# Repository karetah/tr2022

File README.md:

This is a tracktor, baby.

Reverse eng of some board.

Tools:

Kicad, drawio, 
CircuitJS1 http://www.falstad.com/circuit/

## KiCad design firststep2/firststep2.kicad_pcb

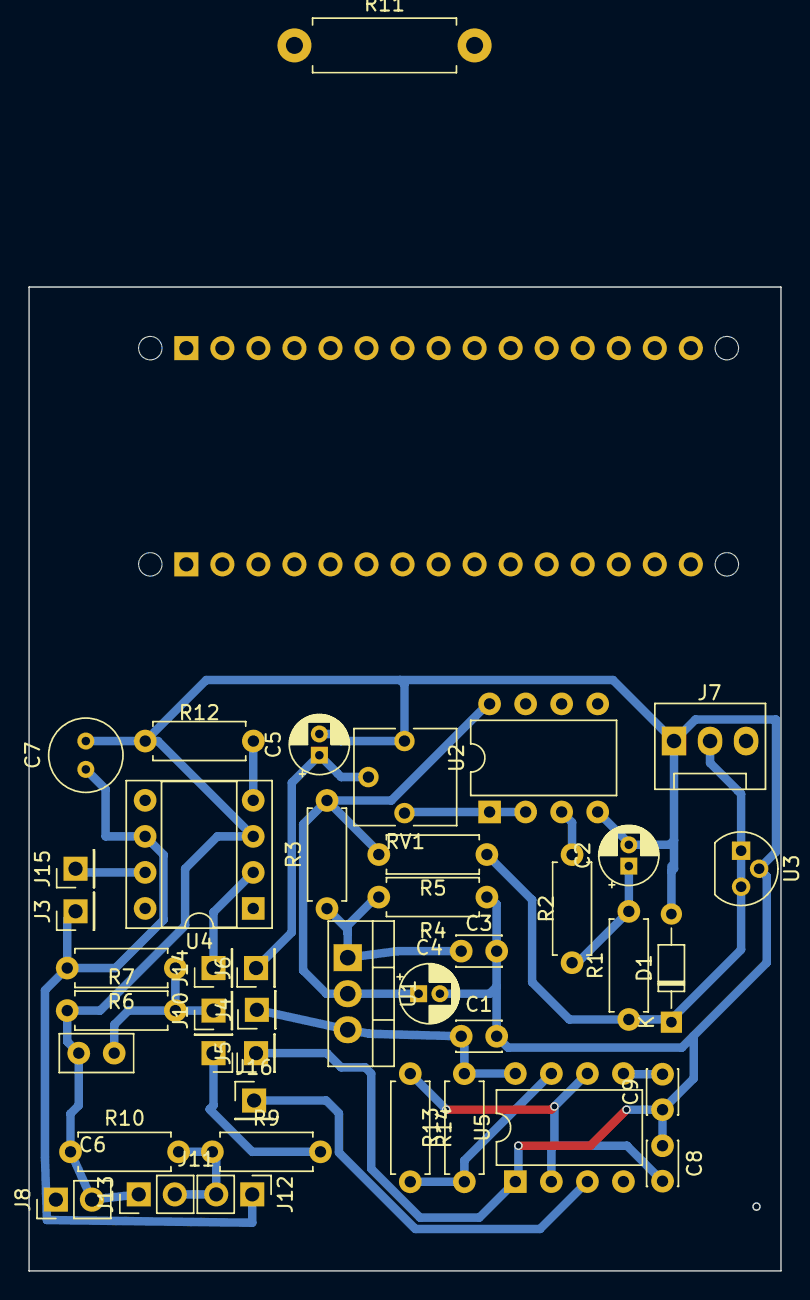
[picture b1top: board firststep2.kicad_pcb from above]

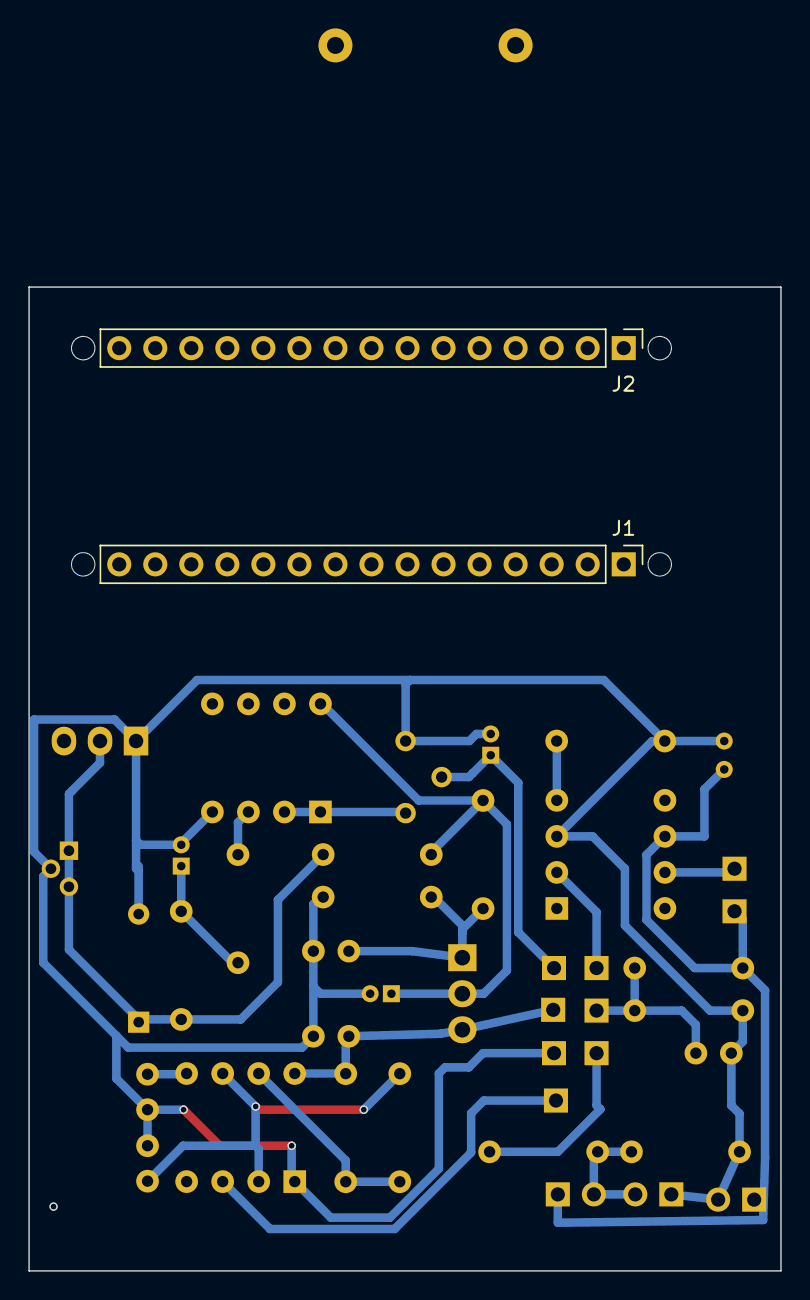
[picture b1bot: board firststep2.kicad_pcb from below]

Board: 2 copper layers, 53.0 x 69.3 mm, 48 parts (2 on the bottom side), 21 nets.

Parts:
C1, C9: 10n; C_Disc_D3.0mm_W2.0mm_P2.50mm
C2: 3,3u; CP_Radial_D4.0mm_P1.50mm
C3: 100n; C_Disc_D3.0mm_W2.0mm_P2.50mm
C4, C5: 1u; CP_Radial_D4.0mm_P1.50mm
C6: 100n; C_Disc_D5.0mm_W2.5mm_P2.50mm
C7: 10u; C_Radial_D5.0mm_H5.0mm_P2.00mm
C8: 6.8n; C_Disc_D3.0mm_W2.0mm_P2.50mm
D1: D_Zener; D_DO-34_SOD68_P7.62mm_Horizontal
J1: Analog; PinHeader_1x15_P2.54mm_Vertical
J2: Conn_01x03_Male; FanPinHeader_1x03_P2.54mm_Vertical
J2#2: Digital; PinHeader_1x15_P2.54mm_Vertical
J3: POWER12; PinHeader_1x01_P2.54mm_Vertical
J4: Conn_5V; PinHeader_1x01_P2.54mm_Vertical
J5: Conn_GND; PinHeader_1x01_P2.54mm_Vertical
J6: Arduino_A6; PinHeader_1x01_P2.54mm_Vertical
J8: BACKLAMP; PinHeader_1x02_P2.54mm_Vertical
J10: Arduino_A7; PinHeader_1x01_P2.54mm_Vertical
J11: Arduino_D6; PinHeader_1x01_P2.54mm_Vertical
J12: RELAY_SW; PinHeader_1x02_P2.54mm_Vertical
J13: RELAY_PWR; PinHeader_1x02_P2.54mm_Vertical
J14: Arduino_D9; PinHeader_1x01_P2.54mm_Vertical
J15: Conn_FET; PinHeader_1x01_P2.54mm_Vertical
J16: Arduino_RX0; PinHeader_1x01_P2.54mm_Vertical
MH1, MH2, MH3, MH4: MountingHole_65mil
R2, R2#2, R3: 330; R_Axial_DIN0207_L6.3mm_D2.5mm_P7.62mm_Horizontal
R4: 470; R_Axial_DIN0207_L6.3mm_D2.5mm_P7.62mm_Horizontal
R5, R13, R14: 1K; R_Axial_DIN0207_L6.3mm_D2.5mm_P7.62mm_Horizontal
R6: 150K; R_Axial_DIN0207_L6.3mm_D2.5mm_P7.62mm_Horizontal
R7, R12: 10K; R_Axial_DIN0207_L6.3mm_D2.5mm_P7.62mm_Horizontal
R9, R10: 22K; R_Axial_DIN0207_L6.3mm_D2.5mm_P7.62mm_Horizontal
R11: 10; R_Axial_DIN0411_L9.9mm_D3.6mm_P12.70mm_Horizontal
RV1: 20K; Potentiometer_Vishay_T73YP_Vertical
U1: LM317_TO-220; TO-220-3_Vertical
U2: TL431LP; TO-92
U2#2: TL072; DIP-8_W7.62mm
U4: MIC4428; DIP-8_W7.62mm_Socket
U5: NE555P; DIP-8_W7.62mm

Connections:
+5V: C1.1, J1.12, J4.1, R13.2, U1.3 (VI), U5.8 (VCC)
/D1/TX: J2#2.15, J16.1, U5.3 (Q)
/accel/A6: C5.1, J6.1, RV1.2
/accel/A7: C6.1, J10.1, R6.1, R7.2
/accel/amp: D1.1 (K), J2.2, R2.1, R5.1, U2.1 (REF), U2.3 (K)
/driver/*D6: J11.1, R9.2
/driver/*D9: J14.1, U4.2 (IN_A)
/~RESET: J1.13, J2#2.13
GND: C1.2, C2.2, C3.2, C4.2, C5.2, C6.2, C7.2, C8.1, C9.1, D1.2 (A), J1.14, J2.1, J2#2.12, J5.1, J8.2, J13.1, R4.1, R7.1, R10.1, R12.1, RV1.1, U2.2 (A), U2#2.4 (V-), U4.3 (GND), U5.1 (GND)
unnamed: C2.1, R2.2, R2#2.1
unnamed: C3.1, R3.1, R4.2, U1.1 (ADJ)
unnamed: C4.1, R3.2, R5.2, U1.2 (VO), U2#2.8 (V+)
unnamed: J12.2, J13.2, R9.1, R10.2
unnamed: J15.1, U4.7 (~OUT_A)
unnamed: R2#2.2, U2#2.3 (+)
unnamed: R12.2, U4.4 (IN_B)
unnamed: RV1.3, U2#2.1, U2#2.2 (-)
unnamed: C8.2, R14.1, U5.2 (TR), U5.6 (THR)
unnamed: C9.2, U5.5 (CV)
unnamed: R13.1, R14.2, U5.7 (DIS)
VCC: C7.1, J1.15, J3.1, J8.1, J12.1, R6.2, U4.6 (V+)

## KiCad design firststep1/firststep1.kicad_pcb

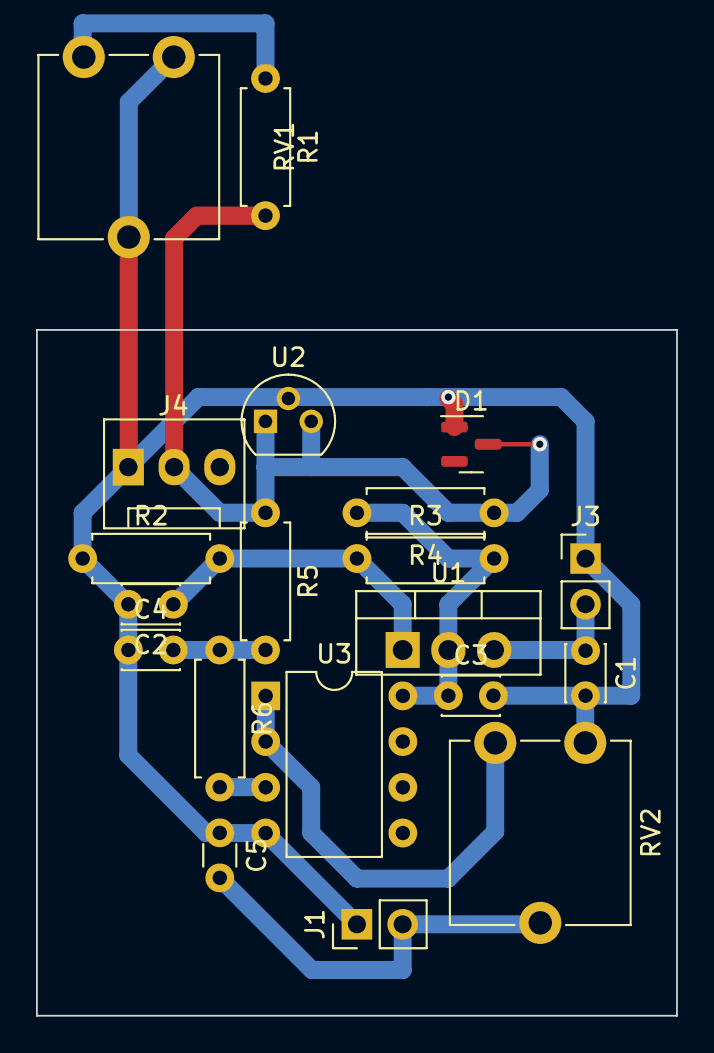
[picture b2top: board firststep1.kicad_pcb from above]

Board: 2 copper layers, 35.6 x 38.1 mm, 20 parts (0 on the bottom side), 10 nets.

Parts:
C1: 10u; C_Disc_D3.0mm_W2.0mm_P2.50mm
C2: 0,47u; C_Disc_D3.0mm_W2.0mm_P2.50mm
C3, C4: 1u; C_Disc_D3.0mm_W2.0mm_P2.50mm
C5: 0,05; C_Disc_D3.0mm_W1.6mm_P2.50mm
D1: SP0502BAHT; SOT-23
J1, J1#2: Conn_01x02; PinHeader_1x02_P2.54mm_Vertical
J2: Conn_01x03_Male; FanPinHeader_1x03_P2.54mm_Vertical
R1: 220; R_Axial_DIN0207_L6.3mm_D2.5mm_P7.62mm_Horizontal
R2: 470; R_Axial_DIN0207_L6.3mm_D2.5mm_P7.62mm_Horizontal
R2#2, R2#3, R2#4: 330; R_Axial_DIN0207_L6.3mm_D2.5mm_P7.62mm_Horizontal
R4: 820; R_Axial_DIN0207_L6.3mm_D2.5mm_P7.62mm_Horizontal
RV1, RV1#2: R_Potentiometer; Potentiometer_ACP_CA9-V10_Vertical
U1: LM317_TO-220; TO-220-3_Vertical
U2: TL431LP; TO-92
U3: LM358; DIP-8_W7.62mm

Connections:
+5V: C1.1, J1#2.2, U1.3 (VI)
ADC: C5.2, J1.2, RV1.2
GND: C1.2, C2.2, C3.2, C4.1, C5.1, D1.1 (K), J1#2.1, J2.1, R2.1, RV1.3, RV1#2.2, RV1#2.3, U2.2 (A), U3.4 (V-)
unnamed: C2.1, R2.2, R2#3.1, U1.1 (ADJ)
unnamed: C3.1, R2#3.2, R4.2, U1.2 (VO), U3.8 (V+)
unnamed: C4.2, R2#2.2, R2#4.1
unnamed: R1.1, RV1#2.1
unnamed: R2#4.2, U3.3 (+)
unnamed: RV1.1, U3.1, U3.2 (-)
opamp: D1.3 (A), J2.2, R1.2, R2#2.1, R4.1, U2.1 (REF), U2.3 (K)

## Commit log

2022-07-29 tracktor2022
    included LM317 and TL431
2022-07-29 REVERSE 12V RELAYS CONTROL
2022-07-29 TL431 subcircuit
    CircuitJS1
    https://github.com/sharpie7/circuitjs1/issues/434
2022-08-02 fix Pot
2022-08-07 add diagram
2022-08-17 add kicad
2022-08-17 added kicad opeamp
2022-08-19 added suppression diode, changed cap values
2022-08-21 many changes
2022-08-22 minor
2022-08-22 added nano docs
2022-08-24 firststep2
2022-08-25 added atmega_logic, changed lm to tl
2022-08-26 update pcb
2022-08-26 minor pcb
2022-08-27 added ino
2022-08-30 add inverter
2022-08-31 change logic
2022-08-31 added NE555 50kHz gen
2022-08-31 drawio change
2022-09-01 minor ino
2022-09-02 add lcd
2022-09-02 revert to wiring
2022-09-03 add wiring
2022-09-03 add simplified.js1
2022-09-05 correct sub
2022-09-09 add some js1
